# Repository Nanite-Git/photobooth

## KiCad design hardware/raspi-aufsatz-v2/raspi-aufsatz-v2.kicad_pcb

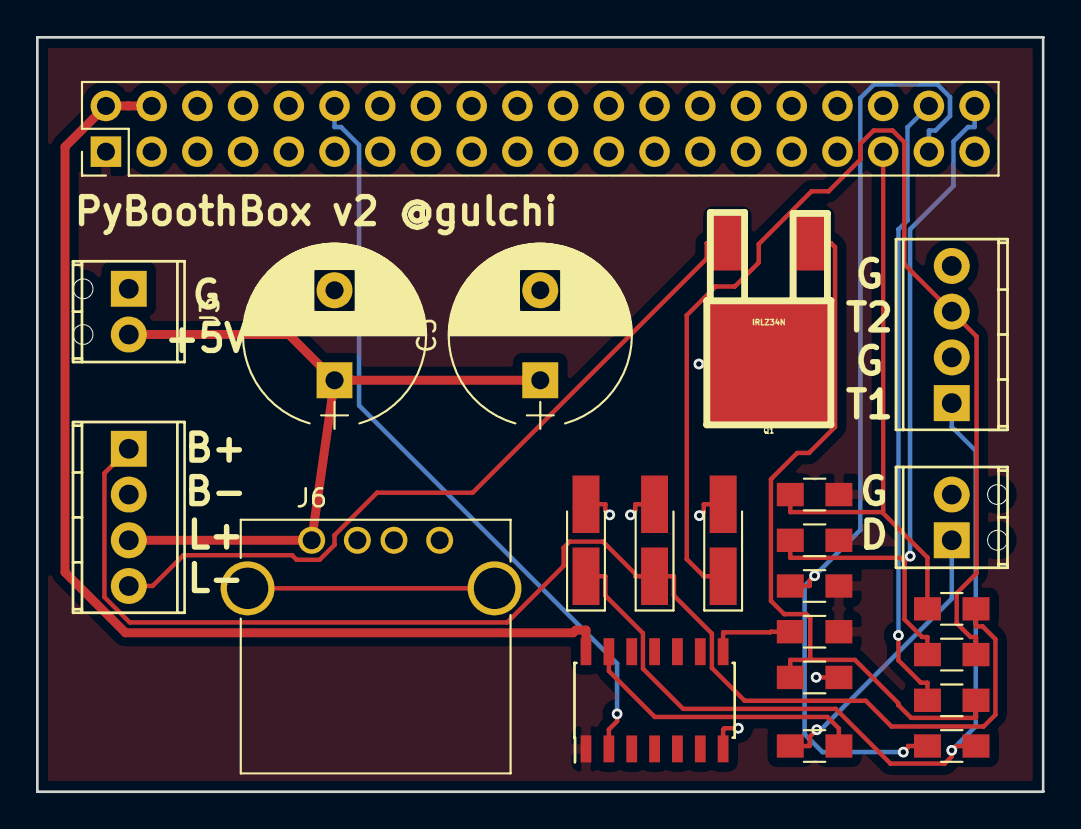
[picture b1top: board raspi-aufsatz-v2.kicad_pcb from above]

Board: 2 copper layers, 55.9 x 41.9 mm, 23 parts (0 on the bottom side), 17 nets.

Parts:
C1, C2, C3: 5uF; CP_Tantalum_Case-S_EIA-3216-12_Hand
C4, C5: 1000uF; CP_Radial_D10.0mm_P5.00mm
J1: Raspberry_Pi_2_3; Pin_Header_Straight_2x20_Pitch2.54mm
J2: Button; TerminalBlock_Phoenix_MPT-2.54mm_4pol
J3: Supply; TerminalBlock_Phoenix_MPT-2.54mm_2pol
J4: Screw_Terminal_01x04; TerminalBlock_Phoenix_MPT-2.54mm_4pol
J5: Data; TerminalBlock_Phoenix_MPT-2.54mm_2pol
J6: USB_A
Q1: IRLZ34N; DPAK
R1, R4, R5, R7, R10: 4k7; R_0805_HandSoldering
R2, R3, R6, R8, R9: 330; R_0805_HandSoldering
U1: TXB0104D; SOIC-14_3.9x8.7mm_Pitch1.27mm

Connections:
+3V3: J1.1, R1.2, R5.2, R7.2, R10.2, U1.1
+5V: J1.2, J1.4, U1.14
+5VD: C4.1, C5.1, J2.3, J3.2, J6.1
BUTTON: J1.35, R1.1, R2.1
GND: C1.2, C2.2, C3.2, C4.2, C5.2, J1.6, J1.9, J1.14, J1.20, J1.25, J1.30, J1.34, J1.39, J2.2, J3.1, J4.2, J4.4, J5.2, J6.4, Q1.3, R4.2, U1.7
LED: J1.38, R3.1
unnamed: C1.1, J2.1, R2.2
unnamed: C2.1, J4.3, R6.2
unnamed: C3.1, J4.1, R8.2
unnamed: J2.4, Q1.2
unnamed: J5.1, R9.1
unnamed: Q1.1, R3.2, R4.1
unnamed: R9.2, U1.13
unnamed: R10.1, U1.8
RGBW_LOW: J1.12, U1.2
TASTER1: J1.40, R5.1, R6.1
TASTER2: J1.37, R7.1, R8.1

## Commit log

2017-08-15 changed textdropbackgound transparent is new and now in comment
2017-08-16 Select right directory in start.sh
2017-08-19 Leds und Buttons integriert USBMount integriert aktuell nur beim Start und noch nicht regelmäßig
2017-08-19 LED Ausgang aktiviert
2017-08-20 Lauflicht angepasst
2018-04-01 Added Hardware Development Path
2018-04-07 Added hardware
    raspi-aufsatz-v2 current version with 5v relais control
2018-04-07 Added README.md
    Renamed Project to PyBoothBox v2
2018-04-14 Hardware raspi-aufsatz-v2 geupdated. Bohrung hinzugefügt und Schraubanschlüsse gedreht.
2018-06-12 Updated for serial conection to arduino upload hook added
2018-06-12 small bugfixes
2018-06-13 added qr code and nextcloud upload
2018-06-13 einzug korrigiert
2018-06-13 updated callback to GPIO.BOTH
2018-06-13 nochmal gpio callback
2018-06-13 Now working with upload and QR code
2018-06-13 Added Arduino Source Code
2018-06-13 run hook file at startup to init everything
2018-06-13 create files in tmp directory
2018-06-13 Added size of merged output file
2018-06-13 changed size of merged output file
2018-06-13 Flash timig angepasst
2018-06-13 Rot Farbe um Blitzlicht gemischt
2018-06-14 Fixed upload success check
2018-06-14 typo
2018-06-14 modified usb copy to check if diretory is writeable
2018-06-14 bugfix
2018-06-14 inetention corrected
2018-06-14 Upload folder will only update folder name after 6 oclock
2018-06-14 Minor Bugfixes (mostly intention)
2018-06-14 another bugfix
2018-06-15 Divided createion of folder on get_download_link
2018-08-02 print-hook.py hinzugefügt
